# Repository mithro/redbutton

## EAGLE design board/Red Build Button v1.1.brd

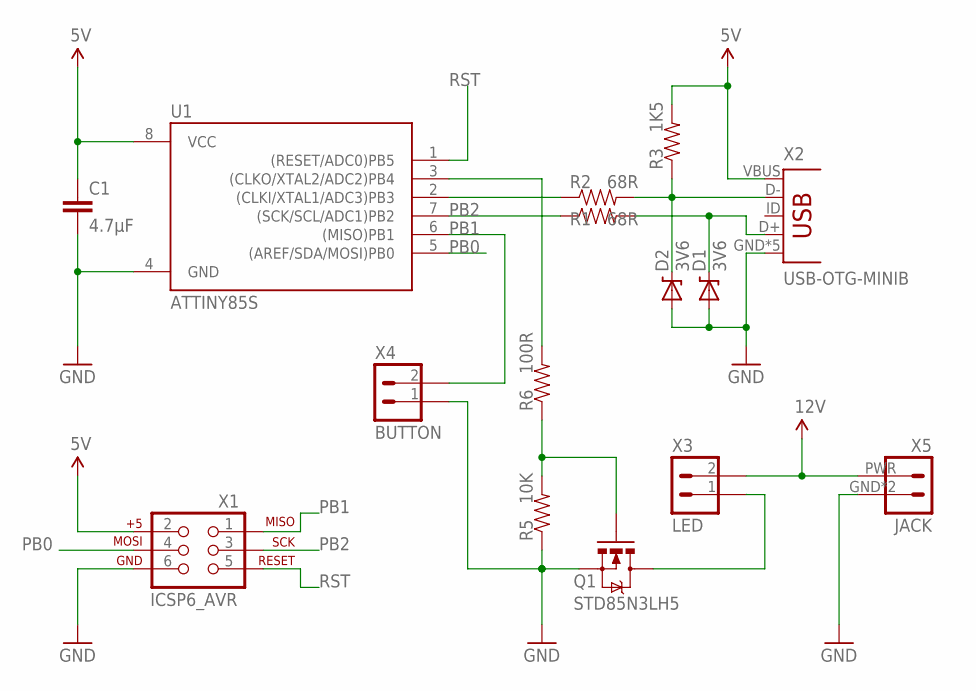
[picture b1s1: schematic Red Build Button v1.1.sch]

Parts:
C1: 4.7µF; 0603-CAP
D1, D2: 3V6; SOD323
Q1: STD85N3LH5; DPAK
R1, R2: 68R; 0603-RES
R3: 1K5; 0603-RES
R5: 10K; 0603-RES
R6: 100R; 0603-RES
U1: ATTINY85S; SOIC8-EIAJ
X1: ICSP6_AVR; 2X3
X2: USB-OTG-MINIB; USB-MINIB-S-SMD
X3: LED; JST-XA-S02B
X4: BUTTON; JST-PA-S02B
X5: JACK; PWR-JACK_PTH

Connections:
5V: C1.1, R3.2, U1.8 (VCC), X1.2 (5V), X2.VBUS
12V: X3.2 (+), X5.PWR (+)
D+: D1.C, R1.2, X2.D+
D-: D2.C, R2.2, R3.1, X2.D-
GATE: Q1.1 (G), R5.2, R6.1
GND: C1.2, D1.A, D2.A, Q1.3 (S), R5.1, U1.4 (GND), X1.6 (GND), X2.GND, X2.GND@2 (GND), X2.GND@3 (GND), X2.GND@4 (GND), X2.GND@5 (GND), X4.1 (-), X5.GND (-), X5.GND@2 (-)
LED-: Q1.4 (D), X3.1 (-)
PB0: U1.5 ((AREF/SDA/MOSI)PB0), X1.4 (MOSI)
PB1: U1.6 ((MISO)PB1), X1.1 (MISO), X4.2 (+)
PB2: R1.1, U1.7 ((SCK/SCL/ADC1)PB2), X1.3 (SCK)
PB3: R2.1, U1.2 ((CLKI/XTAL1/ADC3)PB3)
PB4: R6.2, U1.3 ((CLKO/XTAL2/ADC2)PB4)
RST: U1.1 ((RESET/ADC0)PB5), X1.5 (RESET)

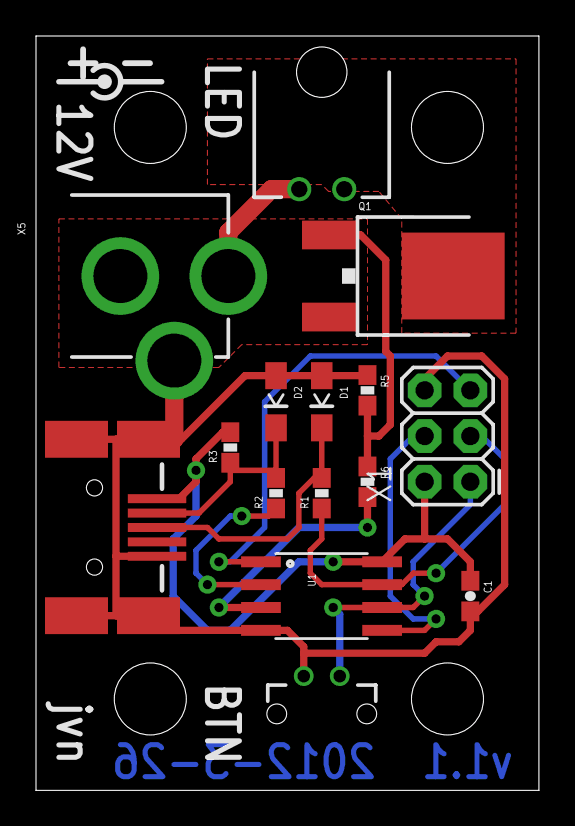
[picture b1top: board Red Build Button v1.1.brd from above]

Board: 2 copper layers, 27.9 x 41.9 mm, 16 parts (0 on the bottom side), 13 nets.

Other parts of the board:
U$1: CENTRE+

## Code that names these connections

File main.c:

/* Copyright (c) 2012, Jan Vaughan
 * All rights reserved.
 *
 * Main application.
 */

#include <avr/interrupt.h>
#include <avr/io.h>
#include <util/delay.h>

#include "common.h"
#include "oscillator.h"
#include "usbdrv.h"

/* Pin assignments:
 * PB0 = unused input (pulled high)
 * PB1 = button input (pulled high)
 * PB2 = USB data
 * PB3 = USB data
 * PB4 = LED output (active high)
 */
#define LED (1 << 4)

/* USB Endpoint 0 (control):
 *   H>D TOGGLE: Stop blinking. Switch LED from current state.
 *   H>D BLINK: Turn LED off, then automatically blink on for 500ms of every 2s.
 *   D>H LED_STATE: Read whether LED is on or off and blinking or fixed. Sends
 *       one byte defined by the masks and values in common.h.
 */


/* Tracks whether blinking is enabled and time into the blink cycle. 255 is disabled, otherwise
 * counts from 0 to 200 centiseconds then loops. LED is enabled from 150 to 200. */
static uint8_t blinking = 255;

/* Byte containing response data for sending out over USB. */
static uint8_t resp;

static usbMsgLen_t handleHostToDevice(usbRequest_t *req);
static usbMsgLen_t handleDeviceToHost(usbRequest_t *req);
static void blink(void);


USB_PUBLIC usbMsgLen_t usbFunctionSetup(uint8_t data[8]) {
  usbRequest_t *req = (usbRequest_t *)data;

  /* We only handle vendor requests involing endpoint 0. We don't expect class requests since we're
   * a vendor specific device, and vusb should have handled standard type requests for us. */
  if ((req->bmRequestType & (USBRQ_TYPE_MASK | USBRQ_RCPT_MASK))
      != (USBRQ_TYPE_VENDOR | USBRQ_RCPT_ENDPOINT)
      || (req->wIndex.bytes[0] & 0x0f) != 0) {
    return 0;
  }
  if ((req->bmRequestType & USBRQ_DIR_MASK) == USBRQ_DIR_HOST_TO_DEVICE) {
    return handleHostToDevice(req);
  } else {
    return handleDeviceToHost(req);
  }
}

static usbMsgLen_t handleHostToDevice(usbRequest_t *req) {
  if (req->bRequest == TOGGLE_REQ) {
    blinking = 255;
    PORTB ^= LED;
  } else if (req->bRequest == BLINK_REQ) {
    PORTB &= ~LED;
    blinking = 0;
  }
  return 0;
}

static usbMsgLen_t handleDeviceToHost(usbRequest_t *req) {
  if (req->bRequest == LED_STATE_REQ) {
    resp = ((PORTB & LED) ? LED_ON : LED_OFF)
        | (blinking == 255 ? FIXED_MODE : BLINK_MODE);
    usbMsgPtr = &resp;
    /* Both USB and AVR words are little endian. */
    return req->wLength.word >= 1 ? 1 : 0;
  } else {
    return 0;
  }
}

static void blink(void) {
  blinking++;
  if (blinking == 150) {
    PORTB |= LED;
  } else if (blinking >= 200) {
    PORTB &= ~LED;
    blinking = 0;
  }
}

int main(void) {
  uint8_t i;

  /* LED is output, all other pins are inputs. */
  DDRB = LED;
  /* Enable pullups on inputs other than the USB ones, LED on to start. */
  PORTB = ~USBMASK;

  restoreOscillator();

  /* Disconnect USB 300ms to reset, then connect. */
  usbDeviceDisconnect();
  for (i = 0; i < 20; i++) {
    _delay_ms(15);
  }
  usbDeviceConnect();

  /* Enable USB */
  usbInit();
  sei();

  /* Ready to go, turn off LED and await instruction. */
  PORTB &= ~LED;
  while (1) {
    usbPoll();
    _delay_ms(10);
    if (blinking != 255) {
      blink();
    }
  }

  return 0; /* never reached */
}

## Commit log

2012-09-05 Initial code dump from Jan.
2017-04-27 Adding header descriptions.
2017-04-27 Adding PCB+schematic.
2017-04-27 Adding more info.

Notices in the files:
parts and their libraries:
SparkFun-Passives: Licensing: CC v3.0 Share-Alike You are welcome to use this library for commercial purposes.
